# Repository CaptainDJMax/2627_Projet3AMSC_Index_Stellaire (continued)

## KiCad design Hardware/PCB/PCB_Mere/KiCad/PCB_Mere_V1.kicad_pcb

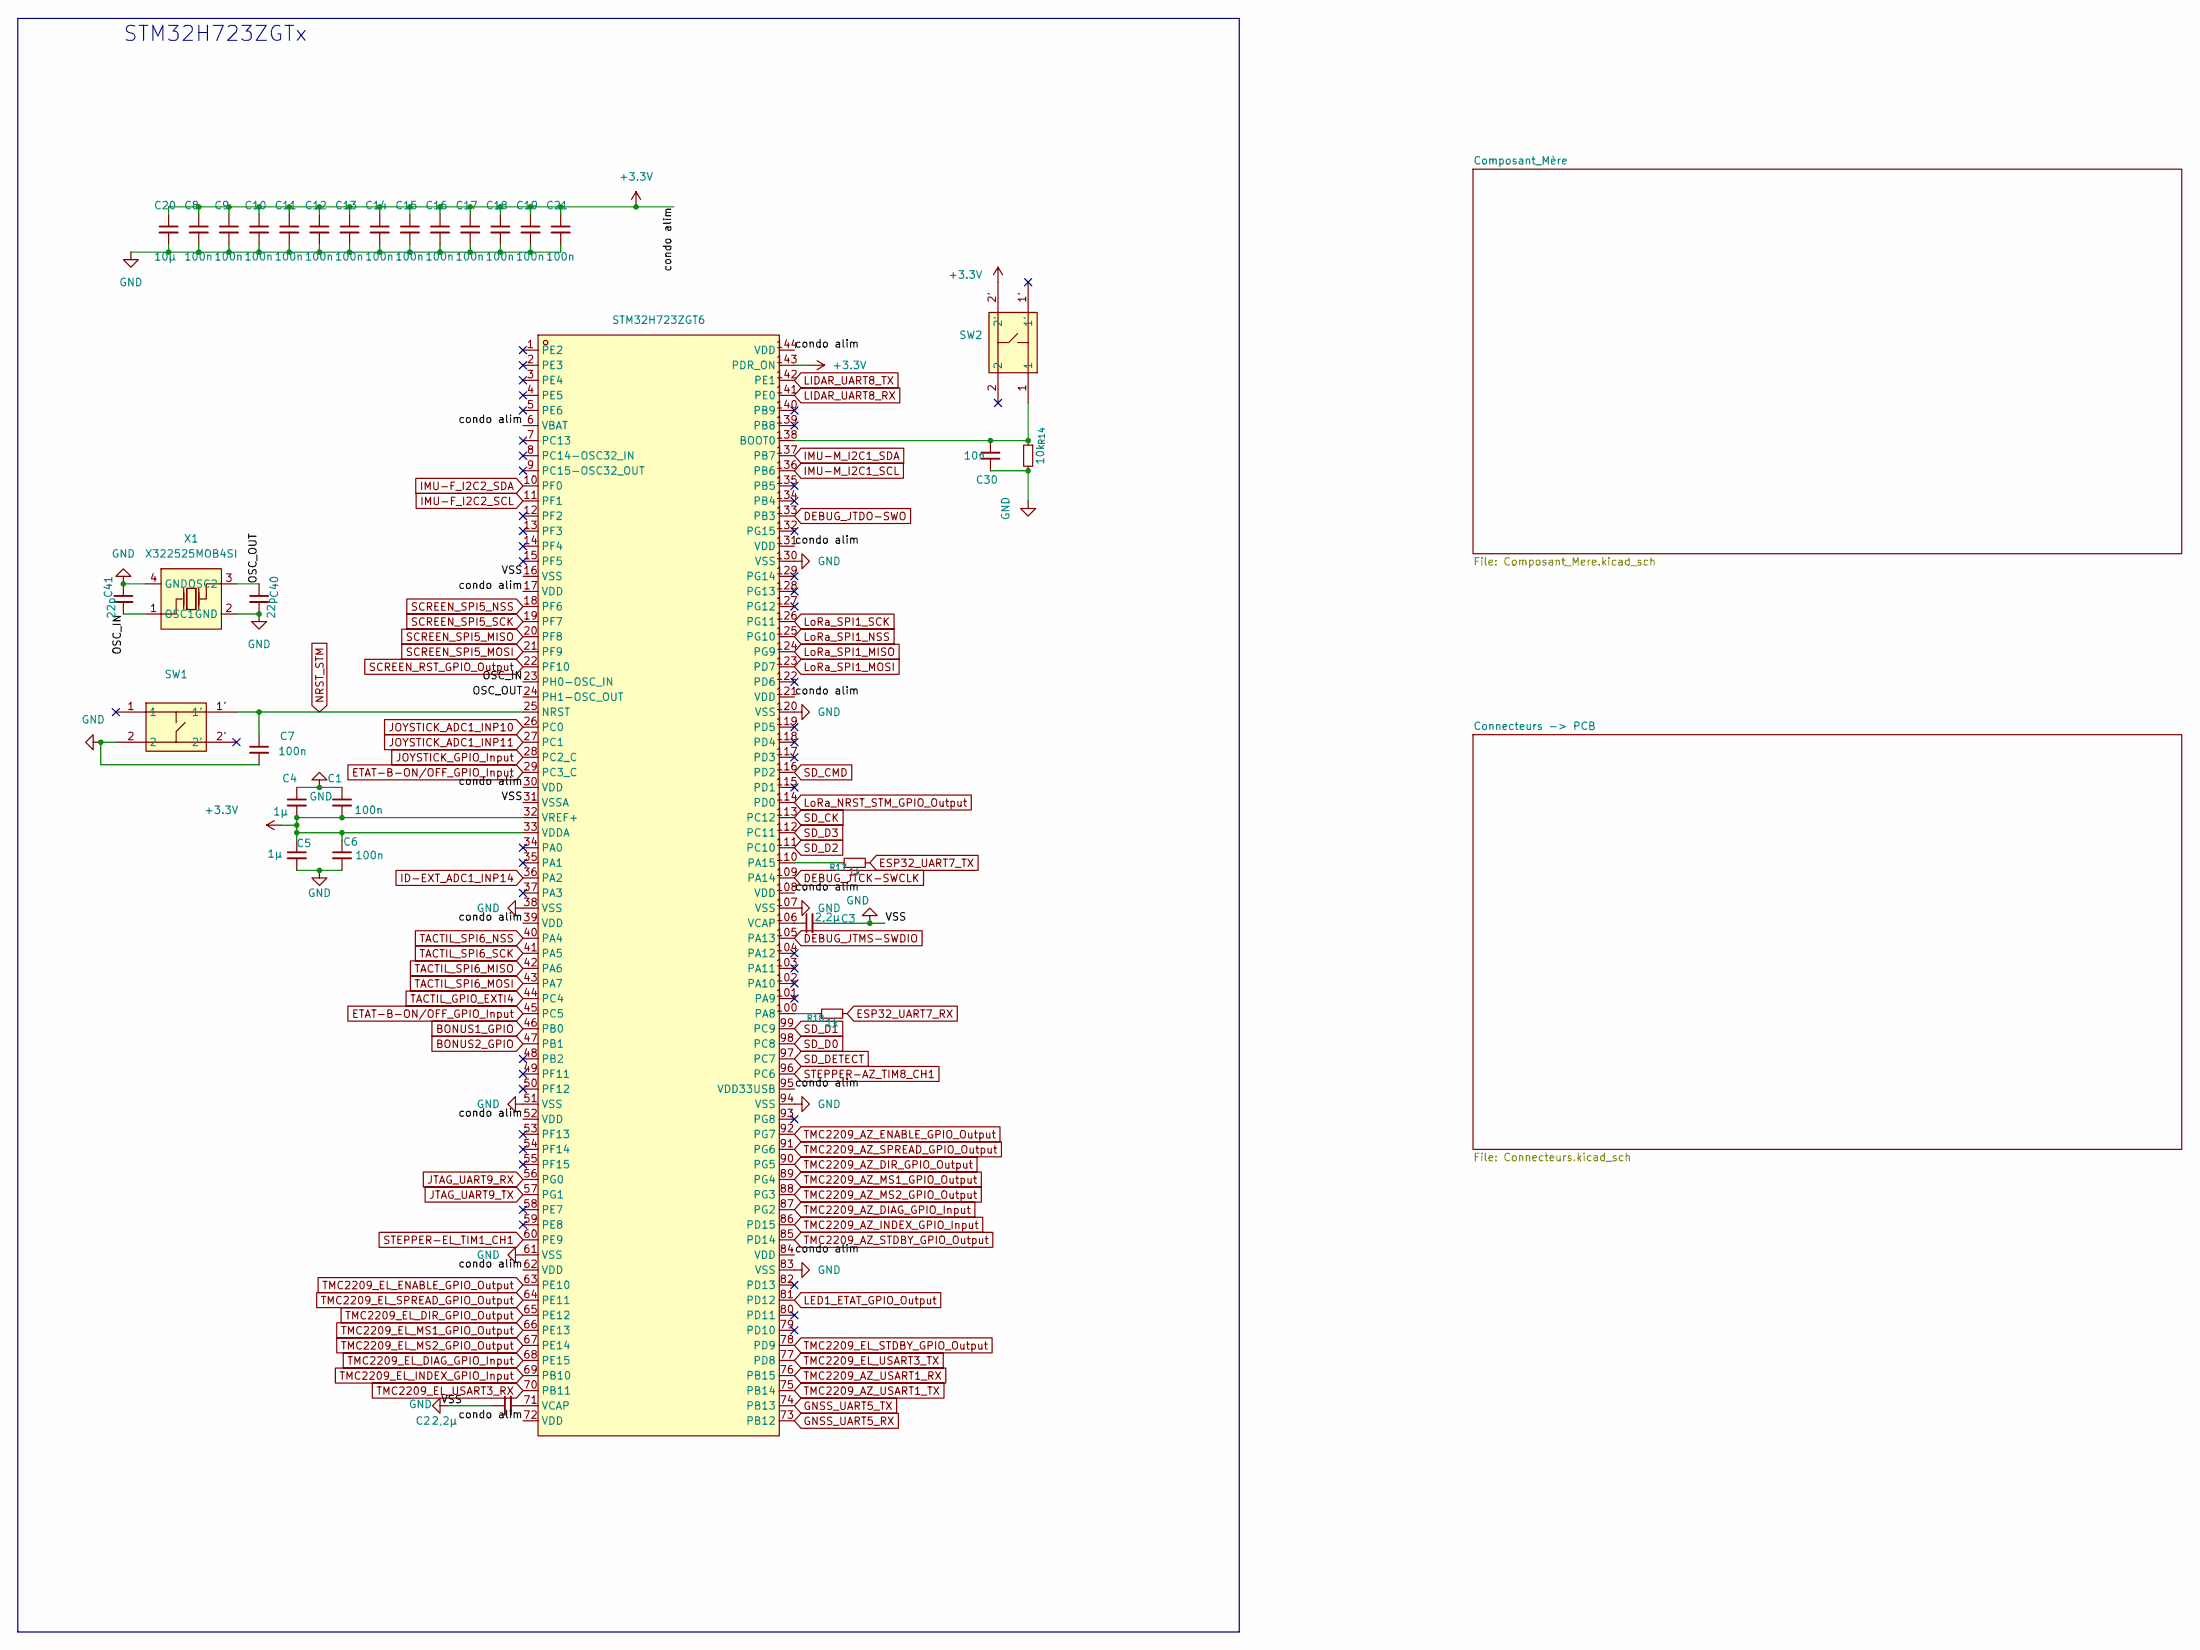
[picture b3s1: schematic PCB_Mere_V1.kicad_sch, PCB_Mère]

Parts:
C1, C6, C7, C8, C9, C10, C11, C12, C13, C14, C15, C16, C17, C18, C19, C21: 100n; C_0402_1005Metric; LCSC Part C1525
C2, C3: 2,2µ; C_0603_1608Metric; LCSC Part C23630
C4, C5: 1µ; C_0402_1005Metric; LCSC Part C52923
C20: 10µ; C_0402_1005Metric; LCSC Part C77000
C30: 10n; C_0402_1005Metric; LCSC Part C15195
C40, C41: 22p; C_0402_1005Metric; LCSC Part C1555
R14: 10k; R_0402_1005Metric; LCSC Part C25744
R17, R18: 1k; R_0402_1005Metric; LCSC Part C11702
SW1, SW2: KEY-SMD_4P-L3.5-W2.9-P1.48-LS4.3-TL; MPN EVPAA202K; LCSC Part C79147
U1: STM32H723ZGT6; LQFP-144_L20.0-W20.0-P0.50-LS22.0-BL; MPN STM32H723ZGT6; LCSC Part C730146
X1: X322525MOB4SI; CRYSTAL-SMD_4P-L3.2-W2.5-BL; MPN X322525MOB4SI; LCSC Part C9006

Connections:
+3.3V: C1.2, C4.2, C5.1, C6.1, C8.1, C9.1, C10.1, C11.1, C12.1, C13.1, C14.1, C15.1, C16.1, C17.1, C18.1, C19.1, C20.1, C21.1, SW2.2', U1.6 (VBAT), U1.17 (VDD), U1.30 (VDD), U1.32 (VREF+), U1.33 (VDDA), U1.39 (VDD), U1.52 (VDD), U1.62 (VDD), U1.72 (VDD), U1.84 (VDD), U1.95 (VDD33USB), U1.108 (VDD), U1.121 (VDD), U1.131 (VDD), U1.143 (PDR_ON), U1.144 (VDD); also elsewhere on the board
/OSC_IN: C41.2, U1.23 (PH0-OSC_IN), X1.1 (OSC1)
/OSC_OUT: C40.1, U1.24 (PH1-OSC_OUT), X1.3 (OSC2)
BONUS1_GPIO: U1.46 (PB0); also elsewhere on the board
BONUS2_GPIO: U1.47 (PB1); also elsewhere on the board
DEBUG_JTCK-SWCLK: U1.109 (PA14); also elsewhere on the board
DEBUG_JTDO-SWO: U1.133 (PB3); also elsewhere on the board
DEBUG_JTMS-SWDIO: U1.105 (PA13); also elsewhere on the board
ESP32_UART7_RX: R18.2; also elsewhere on the board
ESP32_UART7_TX: R17.2; also elsewhere on the board
ETAT-B-ON/OFF_GPIO_Input: U1.29 (PC3_C), U1.45 (PC5); also elsewhere on the board
GND: C1.1, C2.1, C3.2, C4.1, C5.2, C6.2, C7.2, C8.2, C9.2, C10.2, C11.2, C12.2, C13.2, C14.2, C15.2, C16.2, C17.2, C18.2, C19.2, C20.2, C21.2, C30.1, C40.2, C41.1, R14.2, SW1.2, U1.16 (VSS), U1.31 (VSSA), U1.38 (VSS), U1.51 (VSS), U1.61 (VSS), U1.83 (VSS), U1.94 (VSS), U1.107 (VSS), U1.120 (VSS), U1.130 (VSS), X1.2 (GND), X1.4 (GND); also elsewhere on the board
GNSS_UART5_RX: U1.73 (PB12); also elsewhere on the board
GNSS_UART5_TX: U1.74 (PB13); also elsewhere on the board
ID-EXT_ADC1_INP14: U1.36 (PA2); also elsewhere on the board
IMU-F_I2C2_SCL: U1.11 (PF1); also elsewhere on the board
IMU-F_I2C2_SDA: U1.10 (PF0); also elsewhere on the board
IMU-M_I2C1_SCL: U1.136 (PB6); also elsewhere on the board
IMU-M_I2C1_SDA: U1.137 (PB7); also elsewhere on the board
JOYSTICK_ADC1_INP10: U1.26 (PC0); also elsewhere on the board
JOYSTICK_ADC1_INP11: U1.27 (PC1); also elsewhere on the board
JOYSTICK_GPIO_Input: U1.28 (PC2_C); also elsewhere on the board
JTAG_UART9_RX: U1.56 (PG0); also elsewhere on the board
JTAG_UART9_TX: U1.57 (PG1); also elsewhere on the board
LED1_ETAT_GPIO_Output: U1.81 (PD12); also elsewhere on the board
LIDAR_UART8_RX: U1.141 (PE0); also elsewhere on the board
LIDAR_UART8_TX: U1.142 (PE1); also elsewhere on the board
LoRa_NRST_STM_GPIO_Output: U1.114 (PD0); also elsewhere on the board
LoRa_SPI1_MISO: U1.124 (PG9); also elsewhere on the board
LoRa_SPI1_MOSI: U1.123 (PD7); also elsewhere on the board
LoRa_SPI1_NSS: U1.125 (PG10); also elsewhere on the board
LoRa_SPI1_SCK: U1.126 (PG11); also elsewhere on the board
NRST_STM: C7.1, SW1.1', U1.25 (NRST); also elsewhere on the board
unnamed: C2.2, U1.71 (VCAP)
unnamed: C3.1, U1.106 (VCAP)
unnamed: C30.2, R14.1, SW2.1, U1.138 (BOOT0)
unnamed: R18.1, U1.100 (PA8)
unnamed: R17.1, U1.110 (PA15)
SCREEN_RST_GPIO_Output: U1.22 (PF10); also elsewhere on the board
SCREEN_SPI5_MISO: U1.20 (PF8); also elsewhere on the board
SCREEN_SPI5_MOSI: U1.21 (PF9); also elsewhere on the board
SCREEN_SPI5_NSS: U1.18 (PF6); also elsewhere on the board
SCREEN_SPI5_SCK: U1.19 (PF7); also elsewhere on the board
SD_CK: U1.113 (PC12); also elsewhere on the board
SD_CMD: U1.116 (PD2); also elsewhere on the board
SD_D0: U1.98 (PC8); also elsewhere on the board
SD_D1: U1.99 (PC9); also elsewhere on the board
SD_D2: U1.111 (PC10); also elsewhere on the board
SD_D3: U1.112 (PC11); also elsewhere on the board
SD_DETECT: U1.97 (PC7); also elsewhere on the board
STEPPER-AZ_TIM8_CH1: U1.96 (PC6); also elsewhere on the board
STEPPER-EL_TIM1_CH1: U1.60 (PE9); also elsewhere on the board
TACTIL_GPIO_EXTI4: U1.44 (PC4); also elsewhere on the board
TACTIL_SPI6_MISO: U1.42 (PA6); also elsewhere on the board
TACTIL_SPI6_MOSI: U1.43 (PA7); also elsewhere on the board
TACTIL_SPI6_NSS: U1.40 (PA4); also elsewhere on the board
TACTIL_SPI6_SCK: U1.41 (PA5); also elsewhere on the board
TMC2209_AZ_DIAG_GPIO_Input: U1.87 (PG2); also elsewhere on the board
TMC2209_AZ_DIR_GPIO_Output: U1.90 (PG5); also elsewhere on the board
TMC2209_AZ_ENABLE_GPIO_Output: U1.92 (PG7); also elsewhere on the board
TMC2209_AZ_INDEX_GPIO_Input: U1.86 (PD15); also elsewhere on the board
TMC2209_AZ_MS1_GPIO_Output: U1.89 (PG4); also elsewhere on the board
TMC2209_AZ_MS2_GPIO_Output: U1.88 (PG3); also elsewhere on the board
TMC2209_AZ_SPREAD_GPIO_Output: U1.91 (PG6); also elsewhere on the board
TMC2209_AZ_STDBY_GPIO_Output: U1.85 (PD14); also elsewhere on the board
TMC2209_AZ_USART1_RX: U1.76 (PB15); also elsewhere on the board
TMC2209_AZ_USART1_TX: U1.75 (PB14); also elsewhere on the board
TMC2209_EL_DIAG_GPIO_Input: U1.68 (PE15); also elsewhere on the board
TMC2209_EL_DIR_GPIO_Output: U1.65 (PE12); also elsewhere on the board
TMC2209_EL_ENABLE_GPIO_Output: U1.63 (PE10); also elsewhere on the board
TMC2209_EL_INDEX_GPIO_Input: U1.69 (PB10); also elsewhere on the board
TMC2209_EL_MS1_GPIO_Output: U1.66 (PE13); also elsewhere on the board
TMC2209_EL_MS2_GPIO_Output: U1.67 (PE14); also elsewhere on the board
TMC2209_EL_SPREAD_GPIO_Output: U1.64 (PE11); also elsewhere on the board
TMC2209_EL_STDBY_GPIO_Output: U1.78 (PD9); also elsewhere on the board
TMC2209_EL_USART3_RX: U1.70 (PB11); also elsewhere on the board
TMC2209_EL_USART3_TX: U1.77 (PD8); also elsewhere on the board

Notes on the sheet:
STM32H723ZGTx

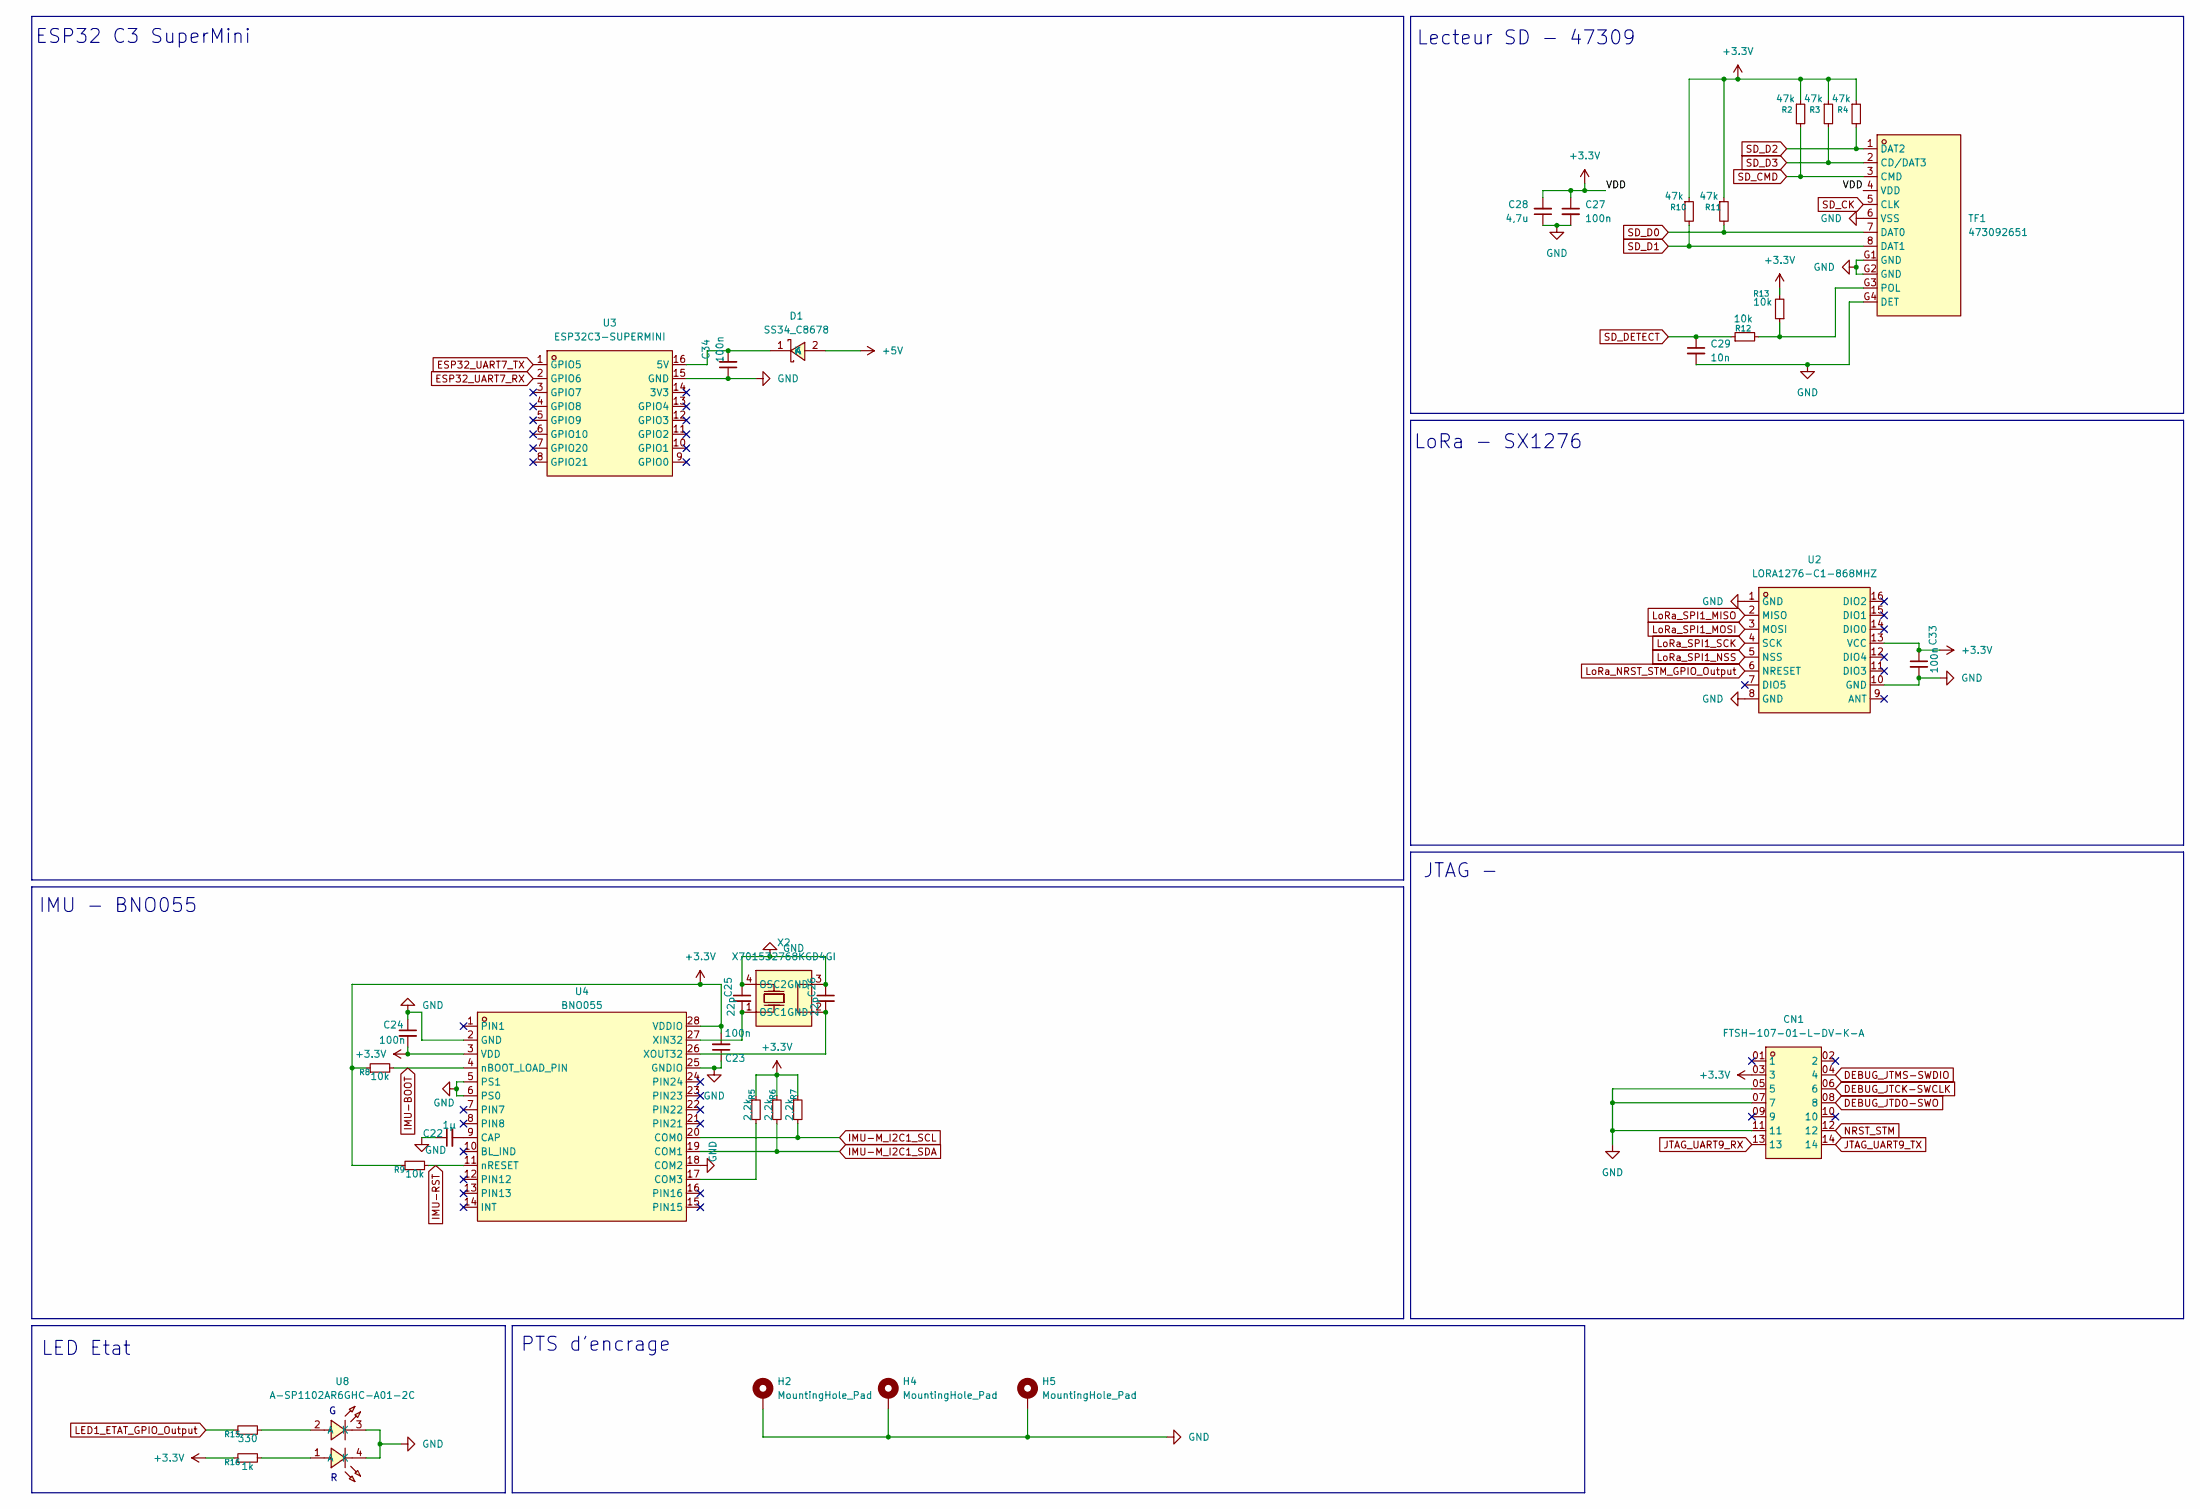
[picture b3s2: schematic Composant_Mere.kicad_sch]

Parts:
C22: 1µ; C_0402_1005Metric; LCSC Part C52923
C23, C24, C27, C33, C34: 100n; C_0402_1005Metric; LCSC Part C1525
C25, C26: 22p; C_0402_1005Metric; LCSC Part C1555
C28: 4,7u; C_0603_1608Metric; LCSC Part C19666
C29: 10n; C_0402_1005Metric; LCSC Part C15195
CN1: FTSH-107-01-L-DV-K-A; HDR-SMD_14P-P1.27_FTSH-107-01-L-DV-K-A; MPN FTSH-107-01-L-DV-K-A; LCSC Part C5563894
D1: SS34_C8678; SMA_L4.3-W2.6-LS5.2-RD; MPN SS34; LCSC Part C8678
H2, H4, H5: MountingHole_Pad; MountingHole_3.2mm_M3_DIN965_Pad_TopBottom
R2, R3, R4, R10, R11: 47k; R_0402_1005Metric; LCSC Part C25792
R5, R6, R7: 2,2k; R_0402_1005Metric; LCSC Part C25879
R8, R9, R12, R13: 10k; R_0402_1005Metric; LCSC Part C25744
R15: 330; R_0402_1005Metric; LCSC Part C25104
R16: 1k; R_0402_1005Metric; LCSC Part C11702
TF1: 473092651; TF-SMD_47309-2285; MPN 473092651; LCSC Part C587826
U2: LORA1276-C1-868MHZ; COMM-SMD_LORA1276-C1-915MHZ; MPN lora1276-C1-868MHz; LCSC Part C3001532
U3: ESP32C3-SUPERMINI; COMM-SMD_16P-L22.5-W18.0-P2.54-TL; MPN ESP32C3-SuperMini; LCSC Part C9900147397
U4: BNO055; LGA-28_L5.2-W3.8-P0.50-BL; MPN BNO055; LCSC Part C93216
U8: A-SP1102AR6GHC-A01-2C; LED-SMD_4P-L3.0-W1.5_A-SP1102AR6GHC-A01-2C; MPN A-SP1102AR6GHC-A01-2C; LCSC Part C5160724
X2: X701532768KGD4GI; MC-146_4P-L6.7-W1.5-P0.85-BL; MPN X701532768KGD4GI; LCSC Part C52084

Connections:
+3.3V: C23.2, C24.2, C27.1, C28.2, C33.1, CN1.03 (3), R2.1, R3.1, R4.1, R5.1, R6.1, R7.1, R8.1, R9.1, R10.1, R11.1, R13.2, R16.1, TF1.4 (VDD), U2.13 (VCC), U4.3 (VDD), U4.28 (VDDIO); also elsewhere on the board
+5V: D1.2 (A); also elsewhere on the board
DEBUG_JTCK-SWCLK: CN1.06 (6); also elsewhere on the board
DEBUG_JTDO-SWO: CN1.08 (8); also elsewhere on the board
DEBUG_JTMS-SWDIO: CN1.04 (4); also elsewhere on the board
ESP32_UART7_RX: U3.2 (GPIO6); also elsewhere on the board
ESP32_UART7_TX: U3.1 (GPIO5); also elsewhere on the board
GND: C22.1, C23.1, C24.1, C25.1, C26.1, C27.2, C28.1, C29.2, C33.2, C34.1, CN1.05 (5), CN1.07 (7), CN1.11, H2.1 (1_1), H4.1 (1_1), H5.1 (1_1), TF1.6 (VSS), TF1.G1 (GND), TF1.G2 (GND), TF1.G4 (DET), U2.1 (GND), U2.8 (GND), U2.10 (GND), U3.15 (GND), U4.2 (GND), U4.5 (PS1), U4.6 (PS0), U4.18 (COM2), U4.25 (GNDIO), U8.3 (K), U8.4 (K), X2.3 (GND), X2.4 (OSC2); also elsewhere on the board
IMU-BOOT: R8.2, U4.4 (nBOOT_LOAD_PIN)
IMU-M_I2C1_SCL: R7.2, U4.20 (COM0); also elsewhere on the board
IMU-M_I2C1_SDA: R6.2, U4.19 (COM1); also elsewhere on the board
IMU-RST: R9.2, U4.11 (nRESET)
JTAG_UART9_RX: CN1.13; also elsewhere on the board
JTAG_UART9_TX: CN1.14; also elsewhere on the board
LED1_ETAT_GPIO_Output: R15.1; also elsewhere on the board
LoRa_NRST_STM_GPIO_Output: U2.6 (NRESET); also elsewhere on the board
LoRa_SPI1_MISO: U2.2 (MISO); also elsewhere on the board
LoRa_SPI1_MOSI: U2.3 (MOSI); also elsewhere on the board
LoRa_SPI1_NSS: U2.5 (NSS); also elsewhere on the board
LoRa_SPI1_SCK: U2.4 (SCK); also elsewhere on the board
NRST_STM: CN1.12; also elsewhere on the board
unnamed: C34.2, D1.1 (K), U3.16 (5V)
unnamed: R15.2, U8.2 (A)
unnamed: R16.2, U8.1 (A)
unnamed: R12.2, R13.1, TF1.G3 (POL)
unnamed: C22.2, U4.9 (CAP)
unnamed: R5.2, U4.17 (COM3)
unnamed: C25.2, U4.27 (XIN32), X2.1 (OSC1)
unnamed: C26.2, U4.26 (XOUT32), X2.2 (GND)
SD_CK: TF1.5 (CLK); also elsewhere on the board
SD_CMD: R2.2, TF1.3 (CMD); also elsewhere on the board
SD_D0: R11.2, TF1.7 (DAT0); also elsewhere on the board
SD_D1: R10.2, TF1.8 (DAT1); also elsewhere on the board
SD_D2: R4.2, TF1.1 (DAT2); also elsewhere on the board
SD_D3: R3.2, TF1.2 (CD/DAT3); also elsewhere on the board
SD_DETECT: C29.1, R12.1; also elsewhere on the board

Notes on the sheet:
IMU - BNO055
ESP32 C3 SuperMini
PTS d'encrage
LED Etat
JTAG -
LoRa - SX1276
Lecteur SD - 47309

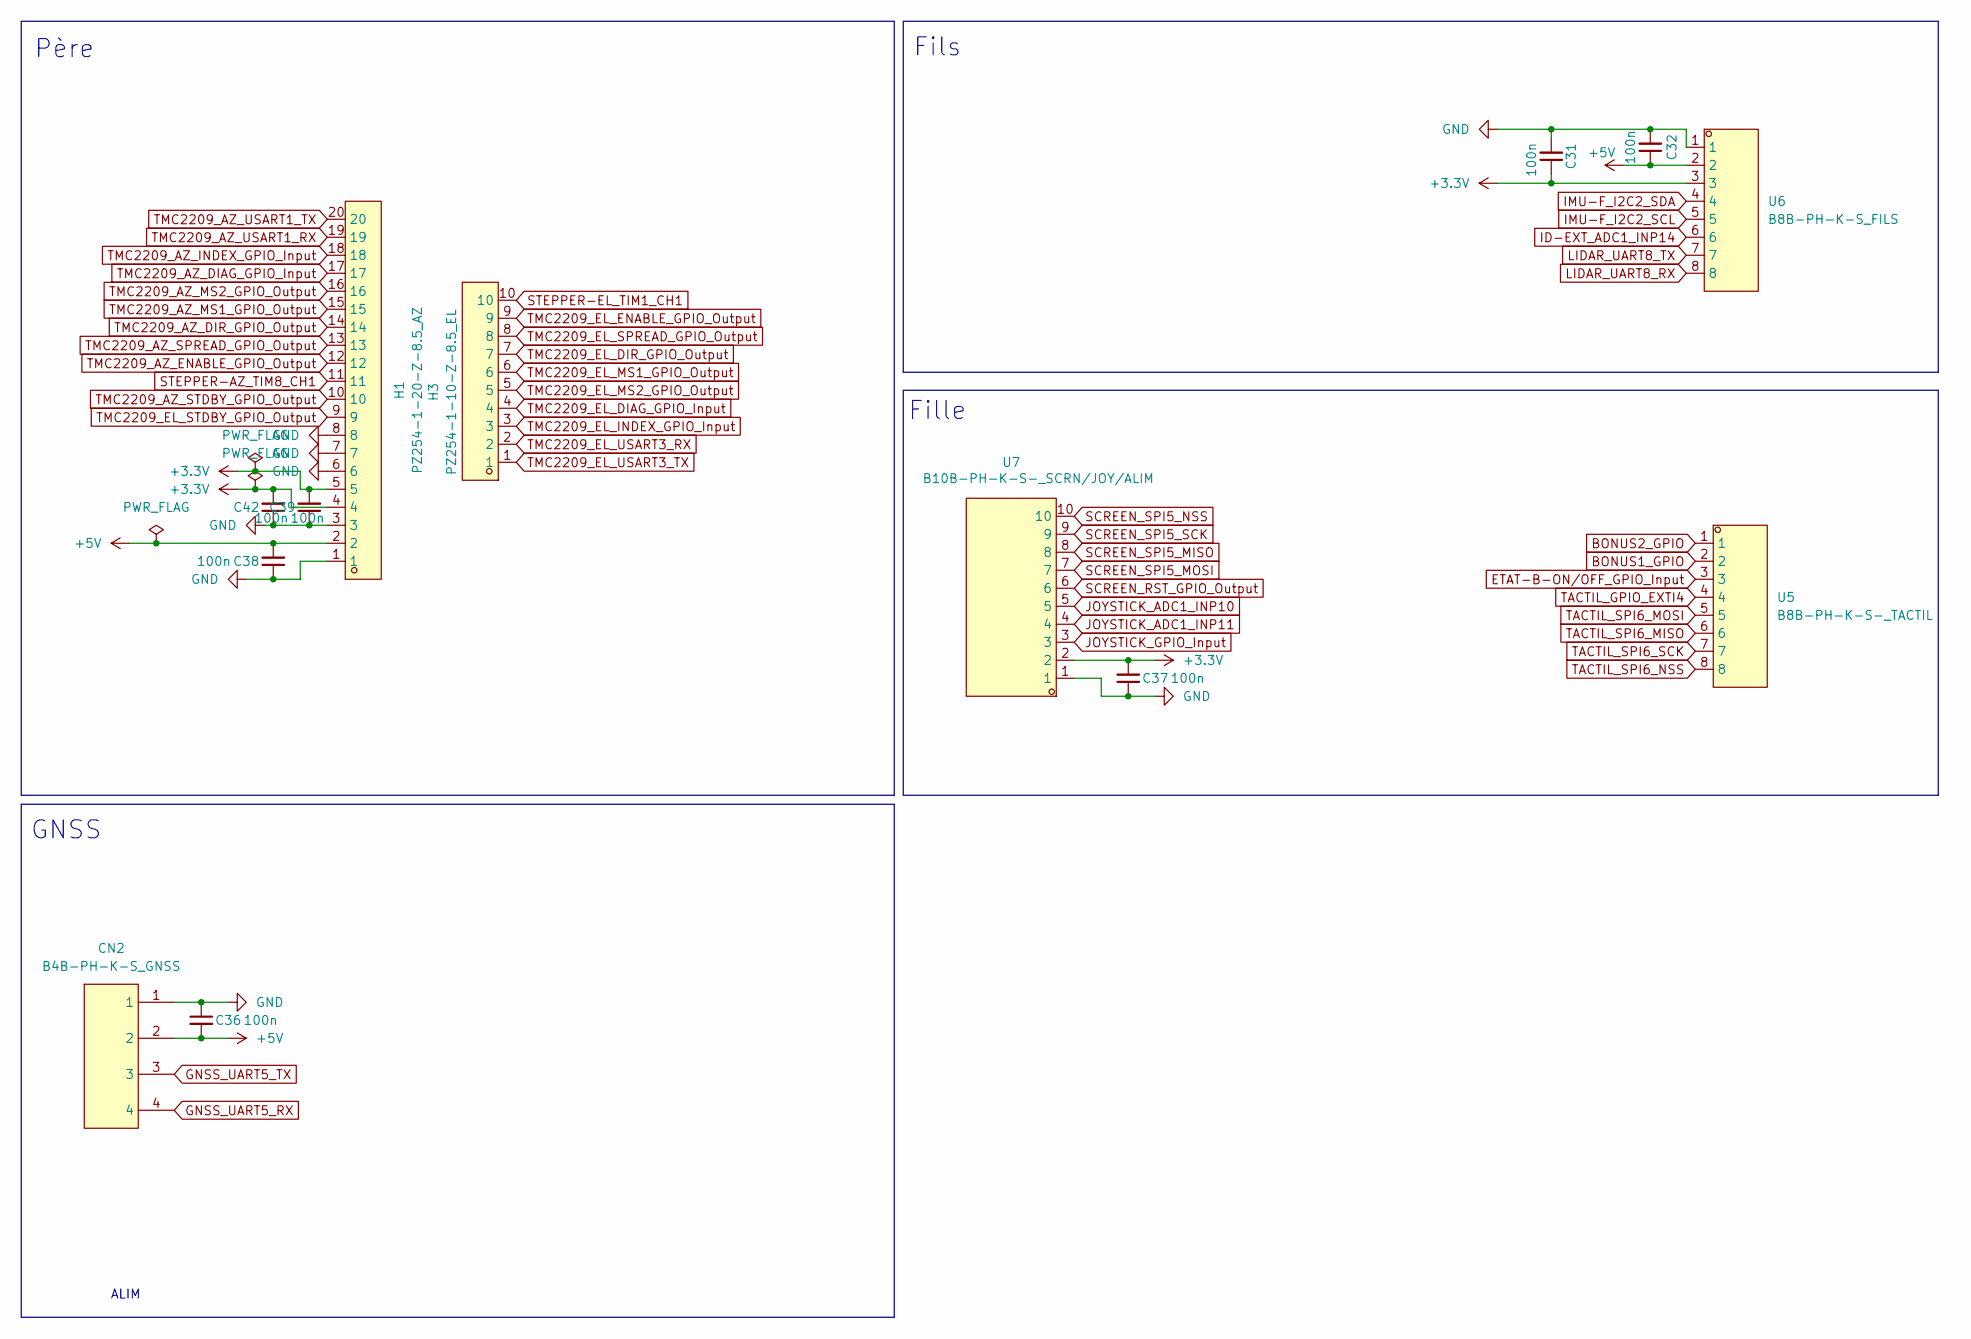
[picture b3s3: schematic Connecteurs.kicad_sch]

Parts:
C31, C32, C36, C37, C38, C39, C42: 100n; C_0402_1005Metric; LCSC Part C1525
CN2: B4B-PH-K-S_GNSS; CONN-TH_B4B-PH-K-S; MPN B4B-PH-K-S(LF)(SN); LCSC Part C131334
H1: PZ254-1-20-Z-8.5_AZ; HDR-TH_20P-P2.54-V-M; MPN PZ254-1-20-Z-8.5; LCSC Part C2894943
H3: PZ254-1-10-Z-8.5_EL; HDR-TH_10P-P2.54-V-M; MPN PZ254-1-10-Z-8.5; LCSC Part C2894933
U5: B8B-PH-K-S-_TACTIL; CONN-TH_B8B-PH-K-S-LF-SN; MPN B8B-PH-K-S(LF)(SN); LCSC Part C157974
U6: B8B-PH-K-S_FILS; CONN-TH_B8B-PH-K-S-LF-SN; MPN B8B-PH-K-S(LF)(SN); LCSC Part C157974
U7: B10B-PH-K-S-_SCRN/JOY/ALIM; CONN-TH_B10B-PH-K-S-LF-SN; MPN B10B-PH-K-S(LF)(SN); LCSC Part C158038

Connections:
+3.3V: C31.1, C37.2, C39.2, C42.2, H1.4, H1.5, U6.3, U7.2; also elsewhere on the board
+5V: C32.1, C36.2, C38.2, CN2.2, H1.2, U6.2; also elsewhere on the board
BONUS1_GPIO: U5.2; also elsewhere on the board
BONUS2_GPIO: U5.1; also elsewhere on the board
ETAT-B-ON/OFF_GPIO_Input: U5.3; also elsewhere on the board
GND: C31.2, C32.2, C36.1, C37.1, C38.1, C39.1, C42.1, CN2.1, H1.1, H1.3, H1.6, H1.7, H1.8, U6.1, U7.1; also elsewhere on the board
GNSS_UART5_RX: CN2.4; also elsewhere on the board
GNSS_UART5_TX: CN2.3; also elsewhere on the board
ID-EXT_ADC1_INP14: U6.6; also elsewhere on the board
IMU-F_I2C2_SCL: U6.5; also elsewhere on the board
IMU-F_I2C2_SDA: U6.4; also elsewhere on the board
JOYSTICK_ADC1_INP10: U7.5; also elsewhere on the board
JOYSTICK_ADC1_INP11: U7.4; also elsewhere on the board
JOYSTICK_GPIO_Input: U7.3; also elsewhere on the board
LIDAR_UART8_RX: U6.8; also elsewhere on the board
LIDAR_UART8_TX: U6.7; also elsewhere on the board
SCREEN_RST_GPIO_Output: U7.6; also elsewhere on the board
SCREEN_SPI5_MISO: U7.8; also elsewhere on the board
SCREEN_SPI5_MOSI: U7.7; also elsewhere on the board
SCREEN_SPI5_NSS: U7.10; also elsewhere on the board
SCREEN_SPI5_SCK: U7.9; also elsewhere on the board
STEPPER-AZ_TIM8_CH1: H1.11; also elsewhere on the board
STEPPER-EL_TIM1_CH1: H3.10; also elsewhere on the board
TACTIL_GPIO_EXTI4: U5.4; also elsewhere on the board
TACTIL_SPI6_MISO: U5.6; also elsewhere on the board
TACTIL_SPI6_MOSI: U5.5; also elsewhere on the board
TACTIL_SPI6_NSS: U5.8; also elsewhere on the board
TACTIL_SPI6_SCK: U5.7; also elsewhere on the board
TMC2209_AZ_DIAG_GPIO_Input: H1.17; also elsewhere on the board
TMC2209_AZ_DIR_GPIO_Output: H1.14; also elsewhere on the board
TMC2209_AZ_ENABLE_GPIO_Output: H1.12; also elsewhere on the board
TMC2209_AZ_INDEX_GPIO_Input: H1.18; also elsewhere on the board
TMC2209_AZ_MS1_GPIO_Output: H1.15; also elsewhere on the board
TMC2209_AZ_MS2_GPIO_Output: H1.16; also elsewhere on the board
TMC2209_AZ_SPREAD_GPIO_Output: H1.13; also elsewhere on the board
TMC2209_AZ_STDBY_GPIO_Output: H1.10; also elsewhere on the board
TMC2209_AZ_USART1_RX: H1.19; also elsewhere on the board
TMC2209_AZ_USART1_TX: H1.20; also elsewhere on the board
TMC2209_EL_DIAG_GPIO_Input: H3.4; also elsewhere on the board
TMC2209_EL_DIR_GPIO_Output: H3.7; also elsewhere on the board
TMC2209_EL_ENABLE_GPIO_Output: H3.9; also elsewhere on the board
TMC2209_EL_INDEX_GPIO_Input: H3.3; also elsewhere on the board
TMC2209_EL_MS1_GPIO_Output: H3.6; also elsewhere on the board
TMC2209_EL_MS2_GPIO_Output: H3.5; also elsewhere on the board
TMC2209_EL_SPREAD_GPIO_Output: H3.8; also elsewhere on the board
TMC2209_EL_STDBY_GPIO_Output: H1.9; also elsewhere on the board
TMC2209_EL_USART3_RX: H3.2; also elsewhere on the board
TMC2209_EL_USART3_TX: H3.1; also elsewhere on the board

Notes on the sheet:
ALIM
Fils
Fille
GNSS
Père

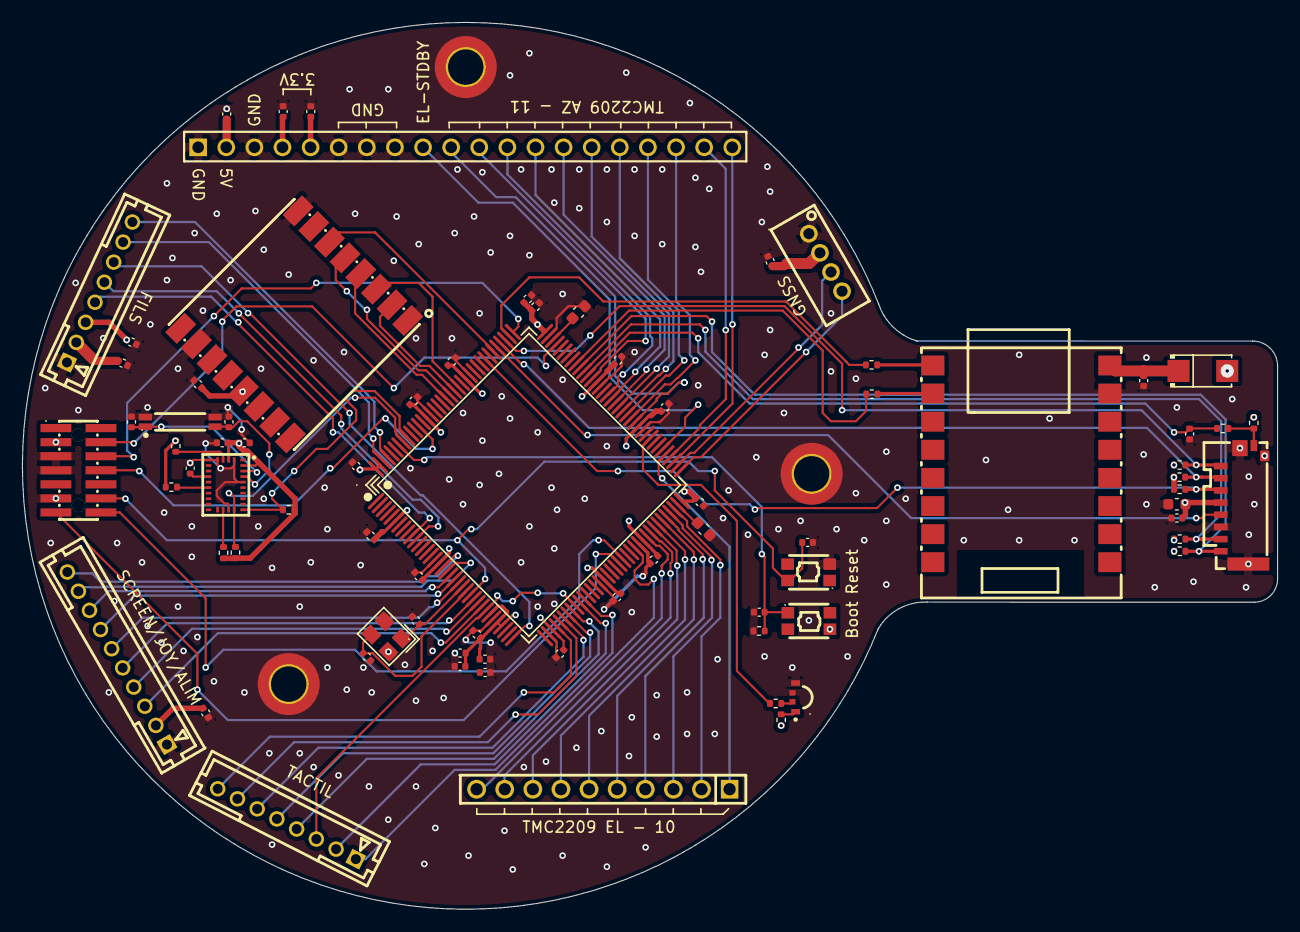
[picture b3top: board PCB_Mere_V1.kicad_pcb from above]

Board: 4 copper layers, 113.4 x 80.1 mm, 79 parts (0 on the bottom side), 88 nets.

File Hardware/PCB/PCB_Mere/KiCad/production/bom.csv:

Designator,Footprint,Quantity,Value,LCSC Part #
"BOOT_BTN-2, NRST_BTN-1",KEY-SMD_4P-L3.5-W2.9-P1.48-LS4.3-TL,2,switch,C79147
"C1, C10, C11, C12, C13, C14, C15, C16, C17, C18, C19, C21, C23, C24, C27, C31, C32, C33, C34, C36, C37, C38, C39, C42, C6, C7, C8, C9",0402,28,100n,C1525
"C2, C3",0603,2,"2,2µ",C23630
C20,0402,1,10µ,C77000
"C22, C4, C5",0402,3,1µ,C52923
"C25, C26, C40, C41",0402,4,22p,C1555
C28,0603,1,"4,7u",C19666
"C29, C30",0402,2,10n,C15195
CN1,HDR-SMD_14P-P1.27_FTSH-107-01-L-DV-K-A,1,FTSH-107-01-L-DV-K-A,C5563894
CN2,CONN-TH_B4B-PH-K-S,1,B4B-PH-K-S_GNSS,C131334
D1,SMA_L4.3-W2.6-LS5.2-RD,1,SS34_C8678,C8678
H1,HDR-TH_20P-P2.54-V-M,1,PZ254-1-20-Z-8.5_AZ,C2894943
H3,HDR-TH_10P-P2.54-V-M,1,PZ254-1-10-Z-8.5_EL,C2894933
"R10, R11, R2, R3, R4",0402,5,47k,C25792
"R12, R13, R14, R8, R9",0402,5,10k,C25744
R15,0402,1,330,C25104
R16,0402,1,1k,C11702
"R17, R18",0402,2,1k,C102683
"R5, R6, R7",0402,3,"2,2k",C25879
TF1,TF-SMD_47309-2285,1,473092651,C587826
U1,LQFP-144_L20.0-W20.0-P0.50-LS22.0-BL,1,STM32H723ZGT6,C730146
U2,COMM-SMD_LORA1276-C1-915MHZ,1,LORA1276-C1-868MHZ,C3001532
U3,COMM-SMD_16P-L22.5-W18.0-P2.54-TL,1,ESP32C3-SUPERMINI,C9900147397
U4,LGA-28_L5.2-W3.8-P0.50-BL,1,BNO055,C93216
U5,CONN-TH_B8B-PH-K-S-LF-SN,1,B8B-PH-K-S-_TACTIL,C157974
U6,CONN-TH_B8B-PH-K-S-LF-SN,1,B8B-PH-K-S_FILS,C157974
U7,CONN-TH_B10B-PH-K-S-LF-SN,1,B10B-PH-K-S-_SCRN/JOY/ALIM,C158038
U8,LED-SMD_4P-L3.0-W1.5_A-SP1102AR6GHC-A01-2C,1,A-SP1102AR6GHC-A01-2C,C5160724
X1,CRYSTAL-SMD_4P-L3.2-W2.5-BL,1,X322525MOB4SI,C9006
X2,MC-146_4P-L6.7-W1.5-P0.85-BL,1,X701532768KGD4GI,C52084

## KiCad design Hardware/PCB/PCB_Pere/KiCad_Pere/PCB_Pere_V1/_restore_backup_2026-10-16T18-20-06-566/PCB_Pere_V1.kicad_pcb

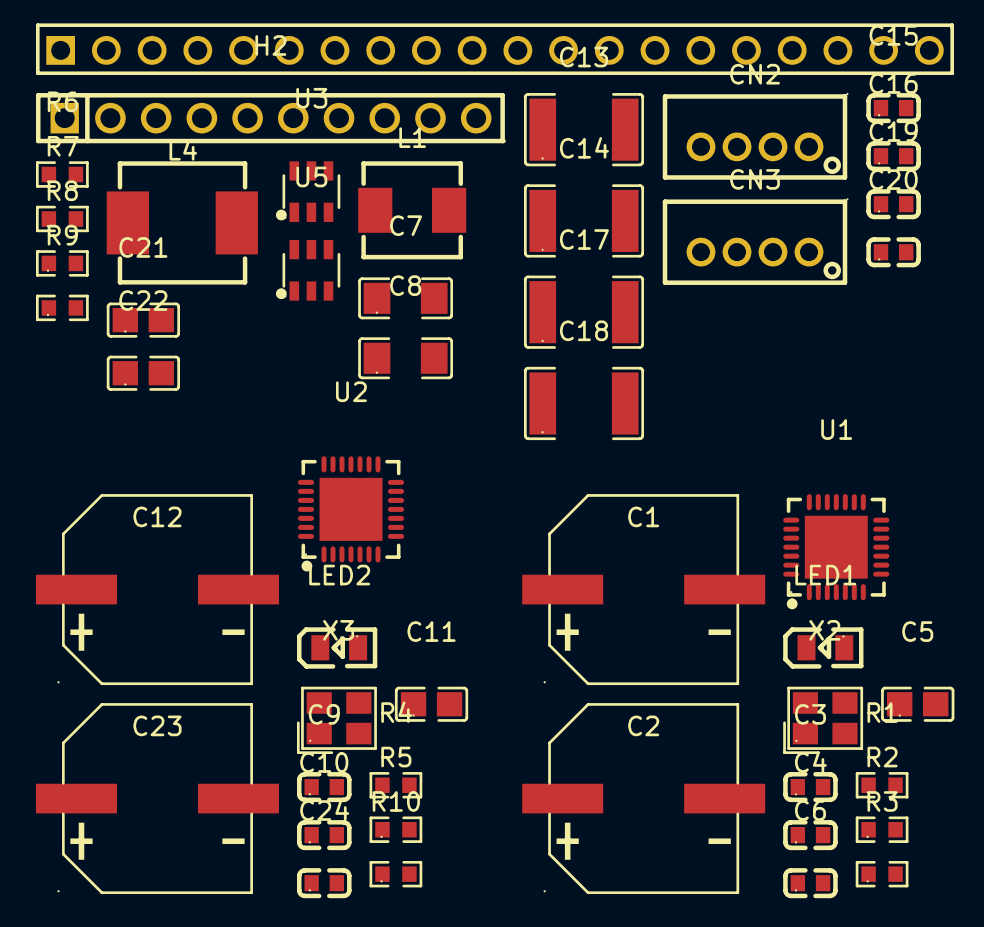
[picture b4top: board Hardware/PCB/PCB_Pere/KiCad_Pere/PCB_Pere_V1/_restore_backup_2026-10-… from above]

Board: 2 copper layers, 48 parts (0 on the bottom side), 36 nets, no tracks yet.

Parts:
C1, C2, C12, C23: 330uF; CAP-SMD_BD10.0-L10.3-W10.3-LS11.0-FD
C3, C4, C6, C9, C10, C15, C16, C19, C20, C24: 100nF; C0603
C5, C11, C21, C22: 22nF; C0805
C7, C8: 2.2uF; C1206
C13, C14, C17, C18: 33uF; C1812
CN2, CN3: B4B-PH-K-S; CONN-TH_B4B-PH-K-S
H1: PZ254-1-20-Z-8.5; HDR-TH_20P-P2.54-V-M
H2: PZ254-1-10-Z-8.5; HDR-TH_10P-P2.54-V-M
L1: 10uH; IND-SMD_L5.4-W5.2_FAUL0530-100MT
L4: 15uF; IND-SMD_L7.0-W6.6_MCW-0650-220
LED1, LED2: Yellow; LED0805-R-RD
R1, R2, R5, R10: 1KΩ; R0603
R3, R4: 100kΩ; R0603
R6: 53.6kR; R0603
R7: 31.6kR; R0603
R8, R9: 10.2kR; R0603
U1, U2: TMC2209-LA-T; QFN-28_L5.0-W5.0-P0.50-BL-EP
U3, U5: Buck LMR51625; SOT-23-6_L2.9-W1.6-P0.95-LS2.9-BL
X2, X3: 12 MHz; CRYSTAL-SMD_4P-L3.2-W2.5-BL

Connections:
+3V3: C6.2, C13.2, C14.2, C21.2, C24.2, L1.2, R7.2, U1.15 (VCC_IO), U2.15 (VCC_IO)
+5V: C17.2, C18.2, C22.2, L4.2, R6.2
+20V: C7.2, C8.2, C19.2, C20.2, U3.2 (EN), U3.3 (VIN), U5.2 (EN), U5.3 (VIN)
/Interfaces/Driver Azimutal1/DIAG: R5.2, U2.2 (ENN), U2.9 (MS1_AD0), U2.11 (DIAG), U2.12 (INDEX), U2.19 (DIR)
/Interfaces/Driver Azimutal1/OA1: CN3.1, U2.24 (OA1)
/Interfaces/Driver Azimutal1/OA2: CN3.2, U2.21 (OA2)
/Interfaces/Driver Azimutal1/OB1: CN3.3, U2.26 (OB1)
/Interfaces/Driver Azimutal1/OB2: CN3.4, U2.1 (OB2)
/Interfaces/Driver Azimutal1/Spread: R4.2, U2.7 (SPREAD)
/Interfaces/Driver Azimutal1/UART_RX: R10.2, U2.14 (PDN_UART)
/Interfaces/Driver Azimutal/DIAG: R2.2, U1.2 (ENN), U1.9 (MS1_AD0), U1.11 (DIAG), U1.12 (INDEX), U1.19 (DIR)
/Interfaces/Driver Azimutal/OA1: CN2.1, U1.24 (OA1)
/Interfaces/Driver Azimutal/OA2: CN2.2, U1.21 (OA2)
/Interfaces/Driver Azimutal/OB1: CN2.3, U1.26 (OB1)
/Interfaces/Driver Azimutal/OB2: CN2.4, U1.1 (OB2)
/Interfaces/Driver Azimutal/Spread: R3.2, U1.7 (SPREAD)
/Interfaces/Driver Azimutal/UART_RX: R1.2, U1.14 (PDN_UART)
/Interfaces/FB_3V3: C21.1, R7.1, R9.2, U3.1 (FB)
/Interfaces/FB_5V: C22.1, R6.1, R8.2, U5.1 (FB)
GND: C1.2, C2.2, C3.1, C6.1, C7.1, C8.1, C10.1, C12.2, C13.1, C14.1, C17.1, C18.1, C19.1, C20.1, C23.2, C24.1, LED1.2 (-), LED2.2 (-), R3.1, R4.1, R8.1, R9.1, U1.3 (GND), U1.18 (GND), U1.29 (EP), U2.3 (GND), U2.18 (GND), U2.29 (EP), U3.4 (GND), U5.4 (GND), X2.2 (GND), X2.4 (GND), X3.2 (GND), X3.4 (GND)
unnamed: C1.1, C2.1, C3.2, C4.2, U1.22 (VS), U1.28 (VS)
unnamed: C9.2, C10.2, C12.1, C23.1, U2.22 (VS), U2.28 (VS)
unnamed: LED1.1 (+), R2.1
unnamed: LED2.1 (+), R5.1
unnamed: U1.13 (CLK), X2.3 (OSC2)
unnamed: C5.1, U1.5 (CPI)
unnamed: C5.2, U1.4 (CPO)
unnamed: C4.1, U1.6 (VCP)
unnamed: U2.13 (CLK), X3.3 (OSC2)
unnamed: C11.1, U2.5 (CPI)
unnamed: C11.2, U2.4 (CPO)
unnamed: C9.1, U2.6 (VCP)
unnamed: C15.1, U3.6 (CB)
unnamed: C15.2, L1.1, U3.5 (SW)
unnamed: C16.1, U5.6 (CB)
unnamed: C16.2, L4.1, U5.5 (SW)
